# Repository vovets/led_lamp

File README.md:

# led_lamp

Slightly overengineered battery powered LED lamp for reading

## Introduction

The project was born when I acquired a battery powered lamp for reading and very soon found its deficiencies.

* It changed brightness as battery drained.
* It had only 2 brightness level, both too bright.
* Its efficiency which I define as a ratio of power coming to LED to power coming from battery is only 0.7.

So I decided to implement my own led driver with mcu control. It actually required some iterations of software and hardware to come up with what is being described here.

## Requirements

* The brightness should be constant as long as the battery voltage under load is higher than some sensible threshold, say 3V. As battery is drained further brightness may gradually decrease.
* When the battery voltage decreases lower than some defined threshold lamp should provide visual indication that battery needs replacement or charging.
* There should be UI for setting the desired brightness level. The brightness levels may be discreet but then there should be enough different levels. The selected brightness level must be kept across the lamp ON-OFF cycles.
* When the battery is completely drained the lamp should clearly indicate this fact and then turn off to prevent battery damage. Lamp should not turn on with a drained battery but provide indication of the flat battery if possible.
 
## Hardware

The lamp consists of "base" with usb connector and batteries, and "head" with a LED panel and a tactile button. The head connected with the base using flexible metallic tube.

### Original hardware

Original electronics consists of two pcbs, one in head and one in base.
The one in the base contains a usb connector, a diode which blocks current from battery to usb VBUS and a 2 Ohm series resistor.
The head pcb contains unmarked chip which obviously provides PWM capability and on/off/mode logic. The LED panel is controlled by a n-channel mosfet. The gate of the mosfet is controlled by the chip. There is also 2 Ohm resistor in series with LED. I assume that the chip is a some obscure uC and there is no LED current limiting except for series resistors.

### Custom hardware

My custom hardware consists of one pcb which contains all the active elements. I also used original pcbs for passive connections. The original base board is used with all parts removed except USB connector. The original head pcb is also cleared of original parts except the button switch and modified using knife and modwire to provide necessary connections. 3 thin wires run inside the connecting tube.

*My custom pcb front and back respectively*

### Custom hardware schematics discussion

The parts I used to design the schematics are those I had at my disposal and/or could easyly source locally.

#### DC-DC converter

This is the module that provides LED current regulation. Efficiency of the whole device depends mostly on this module.
[Converter chip](hw/datasheet/NCP1529.pdf) may be disabled by MCU via EN pin. In disabled state it consumes just 0.3 uA. Output voltage is controlled by voltage on the FB pin. It is connected to the LED current amplifier.

#### LED current amplifier

The LED current amlifier is built using [MCP6001R](hw/datasheet/MCP6001_1R_1U_2_4.pdf "MCP6001R") CMOS opamp. It amplifies voltage drop on 0.1 Ohm current sensing resistor *R7*, which is fed to the non-inverting input. The non-inverting input is also biased by the DAC module output voltage via *R2*. This arrangement allows to set current regulation point by programming DAC output. When DAC output is 0V, amplifier outputs 0.6V for 250mA LED current. When the voltage on DAC output is at max, which is slightly below 2.5V, the current regulated at approximately 10mA point. It corresponds to the lowest brightness of the lamp.
So the maximum current is 250mA and the minimum is 10mA.

#### DAC

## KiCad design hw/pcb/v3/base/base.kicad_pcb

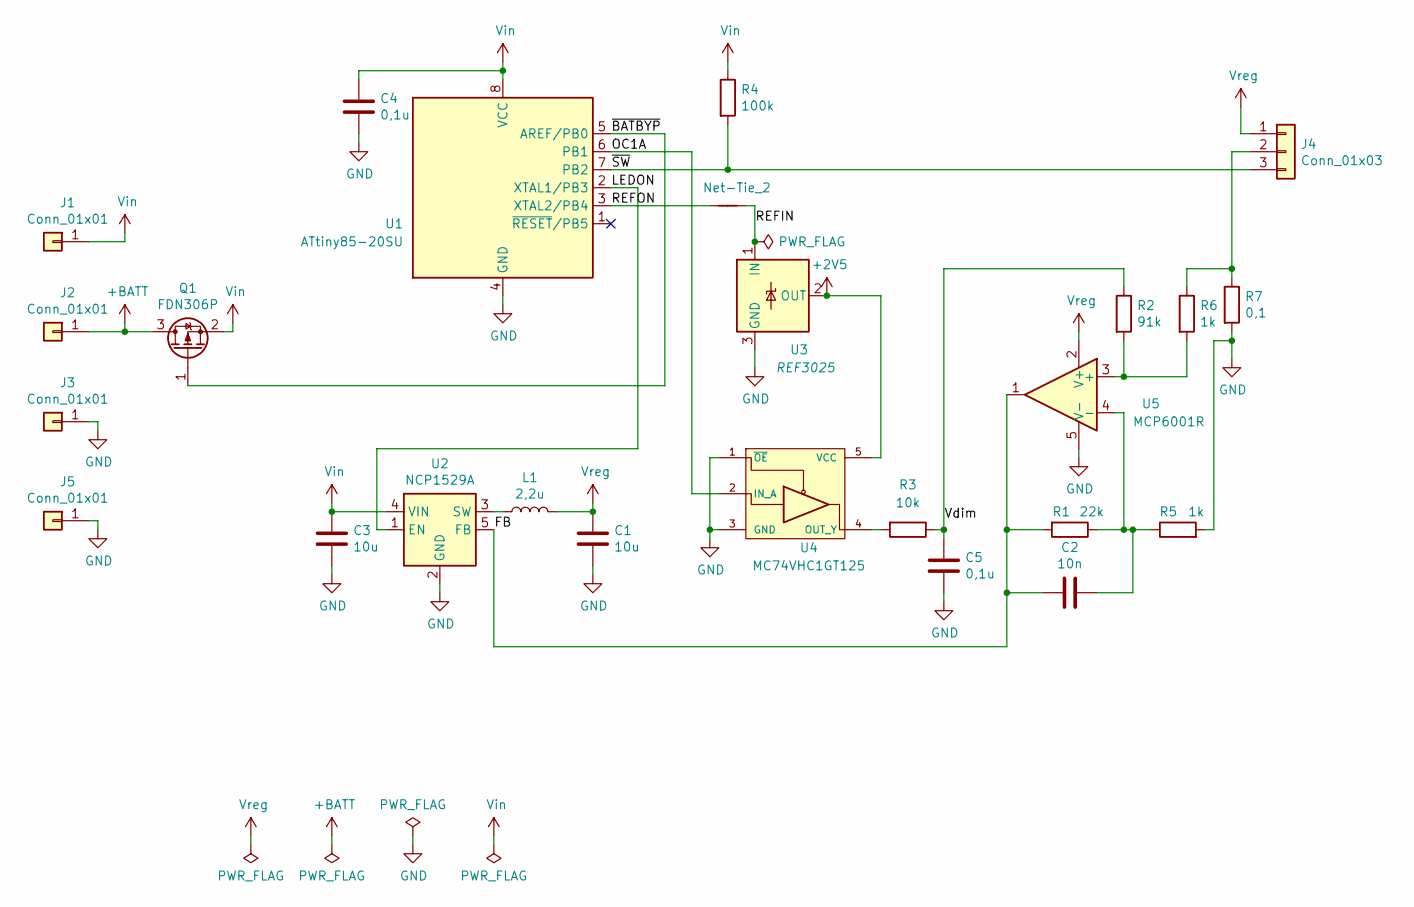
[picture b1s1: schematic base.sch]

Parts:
C1, C3: 10u; C_0805_2012Metric
C2: 10n; C_0805_2012Metric
C4, C5: 0,1u; C_0805_2012Metric
J1, J2, J3, J5: Conn_01x01; SolderWirePad_1x01_SMD_1x2mm
J4: Conn_01x03; SolderWirePad_1x03_SMD_1x2mm
L1: 2,2u; L_1812_4532Metric
NT1: Net-Tie_2; NetTie-2_SMD_Pad0.5mm
Q1: FDN306P; SOT-23
R1: 22k; R_0805_2012Metric
R2: 91k; R_0805_2012Metric
R3: 10k; R_0805_2012Metric
R4: 100k; R_0805_2012Metric
R5, R6: 1k; R_0805_2012Metric
R7: 0,1; R_0805_2012Metric
U1: ATtiny85-20SU; SOIJ-8_5.3x5.3mm_P1.27mm
U2: NCP1529A; SOT-23-5
U3: REF3025; SOT-23
U4: MC74VHC1GT125; SOT-23-5
U5: MCP6001R; SOT-23-5

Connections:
+2V5: U3.2 (OUT), U4.5 (VCC)
+BATT: J2.1, Q1.3 (D)
/FB: C2.2, R1.2, U2.5 (FB), U5.1
/LEDON: U1.2 (XTAL1/PB3), U2.1 (EN)
/OC1A: U1.6 (PB1), U4.2 (IN_A)
/REFIN: NT1.2, U3.1 (IN)
/REFON: NT1.1, U1.3 (XTAL2/PB4)
/Vdim: C5.1, R2.1, R3.1
/~BATBYP: Q1.1 (G), U1.5 (AREF/PB0)
/~SW: J4.3, R4.2, U1.7 (PB2)
GND: C1.2, C3.2, C4.2, C5.2, J3.1, J5.1, R5.2, R7.2, U1.4 (GND), U2.2 (GND), U3.3 (GND), U4.1 (~OE), U4.3 (GND), U5.5 (V-)
unnamed: C2.1, R1.1, R5.1, U5.4 (-)
unnamed: J4.2, R6.1, R7.1
unnamed: L1.1, U2.3 (SW)
unnamed: R2.2, R6.2, U5.3 (+)
unnamed: R3.2, U4.4 (OUT_Y)
Vin: C3.1, C4.1, J1.1, Q1.2 (S), R4.1, U1.8 (VCC), U2.4 (VIN)
Vreg: C1.1, J4.1, L1.2, U5.2 (V+)

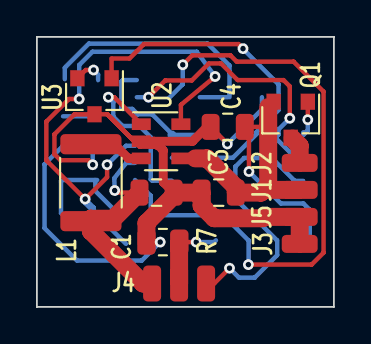
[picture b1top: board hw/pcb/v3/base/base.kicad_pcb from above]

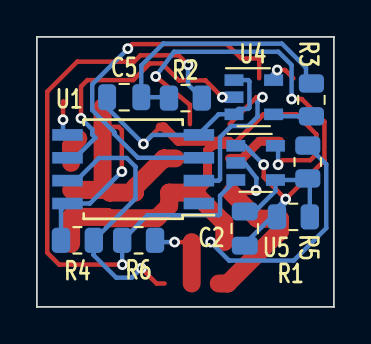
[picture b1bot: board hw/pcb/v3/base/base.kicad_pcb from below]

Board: 2 copper layers, 16.5 x 15.0 mm, 25 parts (11 on the bottom side), 18 nets.

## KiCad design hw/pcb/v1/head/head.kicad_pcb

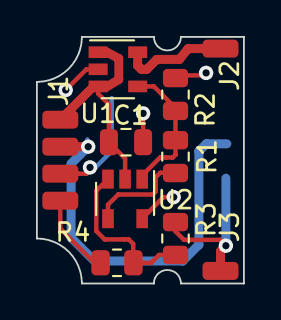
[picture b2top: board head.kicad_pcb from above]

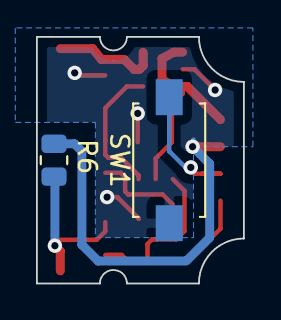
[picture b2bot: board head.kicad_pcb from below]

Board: 2 copper layers, 11.5 x 13.7 mm, 12 parts (2 on the bottom side), 9 nets.

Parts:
C1: 100n; C_0805_2012Metric
J1: Conn_01x04; SolderWirePad_1x04_SMD_1x2mm
J2, J3: Conn_01x01; SolderWirePad_1x01_SMD_1x2mm
R1: 39k; R_0805_2012Metric
R2, R3: 1k; R_0805_2012Metric
R4: 150k; R_0805_2012Metric
R6: 0,1; R_0805_2012Metric
SW1: SW_Push; SW_SPST_UNKNOWN
U1: TPS73601DBV; SOT-23-5
U2: MCP6001R; SOT-23-5

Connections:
/FB: R1.2, R2.1, U1.4, U2.1
/OUT: J2.1, U1.5
/SW: J1.3, SW1.2
/Vpwm: J1.4, R4.1
GND: C1.2, J1.2, R2.2, R6.2, SW1.1, U1.2, U2.5
unnamed: J3.1, R3.1, R6.1
unnamed: R1.1, U2.4
unnamed: R3.2, R4.2, U2.3
Vreg: C1.1, J1.1, U1.1, U1.3, U2.2

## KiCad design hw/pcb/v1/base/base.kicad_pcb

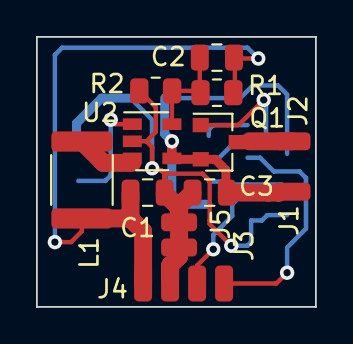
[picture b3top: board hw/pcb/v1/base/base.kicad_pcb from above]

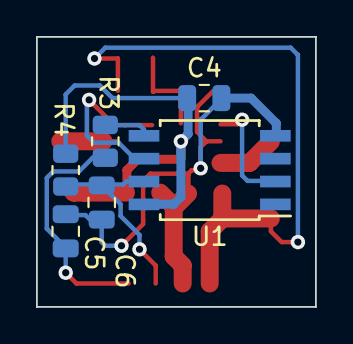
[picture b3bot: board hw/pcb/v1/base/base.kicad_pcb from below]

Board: 2 copper layers, 15.5 x 15.0 mm, 19 parts (6 on the bottom side), 11 nets.

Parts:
C1: 10u; C_0805_2012Metric
C2: 18p; C_0805_2012Metric
C3: 4,7u; C_0805_2012Metric
C4: 0,1u; C_0805_2012Metric
C5, C6: 0.1u; C_0805_2012Metric
J1, J2, J3, J5: Conn_01x01; SolderWirePad_1x01_SMD_1x2mm
J4: Conn_01x04; SolderWirePad_1x04_SMD_1x2mm
L1: 2,2u; L_1812_4532Metric
Q1: FDN306P; SOT-23
R1: 910k; R_0805_2012Metric
R2: 240k; R_0805_2012Metric
R3: 10k; R_0805_2012Metric
R4: 100k; R_0805_2012Metric
U1: ATtiny85-20SU; SOIJ-8_5.3x5.3mm_P1.27mm
U2: NCP1529A; SOT-23-5

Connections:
+BATT: J2.1, Q1.3
/BATBYP: Q1.1, U1.6
/FB: C2.2, R1.2, R2.1, U2.5
/OC0A: R3.2, U1.5
/REGEN: U1.2, U2.1
/SW: C6.1, J4.3, R4.2, U1.7
/Vpwm: C5.1, J4.4, R3.1
GND: C1.2, C3.2, C4.2, C5.2, C6.2, J3.1, J4.2, J5.1, R2.2, U1.4, U2.2
unnamed: L1.1, U2.3
Vin: C3.1, C4.1, J1.1, Q1.2, R4.1, U1.8, U2.4
Vreg: C1.1, C2.1, J4.1, L1.2, R1.1

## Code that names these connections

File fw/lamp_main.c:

#include <lib/timers.h>
#include <lib/blinker.h>
#include "lib/clocks_etc.h"
#include <lib/button.h>
#include <lib/debouncer.h>
#include <lib/pwm.h>
#include <lib/vcc_monitor.h>
#include "debug.h"
#include <lib/stack_check.h>
#include "loop.h"
#include <lib/pwm_animator.h>

#include <stdint.h>
#include <assert.h>

#include <avr/interrupt.h>


#define BATTERY_BYPASS_PIN PB0
#define OC1A_PIN           PB1
#define SWITCH_PIN         PB2
#define LED_ON_PIN         PB3
#define REF_ON_PIN         PB4
#define LED_ON_IS_HIGH true
#define LOW_VOLTAGE_BLINK_PERIOD_S 60

typedef BtnFunc StateFunc;

static void stateOff(BtnEvent e);
static void stateOn(BtnEvent e);
static void stateSetup(BtnEvent e);
static void vccMonitor(uint16_t mV);
static void turnOff_1(void);

typedef struct State {
    enum StateTag {
        StateOff = 0,
        StateOn,
        StateSetup
    } state;
    uint8_t dimLevel;
    uint16_t prevVoltage; // in mV
    uint16_t lowVoltageBlinkCounter;
} State;

static StateFunc state2func[] = {
    stateOff,
    stateOn,
    stateSetup
};


static uint8_t level2dimPercent[] = {
        100, 75, 50, 25, 0
};

static const uint8_t level2dimPercentSize = sizeof(level2dimPercent) / sizeof(level2dimPercent[0]);

static State state;
static Blinker onOffBlinker;
static Blinker vccmBlinker;

static void setState(enum StateTag s) {
    debugTrace2(debugState, s);
    state.state = s;
}

void setupDebug(void) {
    debugTraceEnableIds(
            (uint32_t)0
//            | bits(debugEvPut)
//            | bits(debugEvGet)
//            | bits(debugBtnToggle)
//            | bits(debugBtnEvent)
//            | bits(debugDbnCounter)
//            | bits(debugTimerExpired)
//            | bits(debugTimerSet)
//            | bits(debugTimerCancel)
//            | bits(debugAlarmEnabled)
//            | bits(debugAlarmDisabled)
//            | bits(debugEnterSleep)
//            | bits(debugExitSleep)
//            | bits(debugVccm)
//            | bits(debugState)
//            | bits(debugAdcStartConversion)
            | bits(debugPwm)
    );
}

void initState(void) {
    state.prevVoltage = 0;
}

static void setupPins(void) {
    DDRB |= _BV(OC1A_PIN);
    DDRB |= _BV(BATTERY_BYPASS_PIN);
    DDRB |= _BV(LED_ON_PIN);
    DDRB |= _BV(REF_ON_PIN);
    // disable digital input on all 5 pins except...
    DIDR0 = 0x1FU & ~_BV(SWITCH_PIN);
}

static void setupPCINT(void) {
    PCMSK |= _BV(SWITCH_PIN);
}

static void led(bool on) {
    if (on == LED_ON_IS_HIGH) {
        PORTB |= _BV(LED_ON_PIN);
    } else {
        PORTB &= ~_BV(LED_ON_PIN);
    }
}

static void ref(bool on) {
    if (on) {
        PORTB |= _BV(REF_ON_PIN);
    } else {
        PORTB &= ~_BV(REF_ON_PIN);
    }
}

static void bypass(bool on) {
    if (on) {
        PORTB &= ~_BV(BATTERY_BYPASS_PIN);
    } else {
        PORTB |= _BV(BATTERY_BYPASS_PIN);
    }
}

static uint8_t calculatePwm(uint8_t pwmLevel) {
    uint16_t dimPercent = level2dimPercent[pwmLevel];
    return (dimPercent * 255U) / 100U;
}

static void updatePwm(void) {
    pwmaStart(calculatePwm(state.dimLevel), NULL);
}

static void updateBypass(uint16_t mV) {
    const uint8_t hist = 5;
    int16_t delta = mV - state.prevVoltage;
    if (abs(delta) <= hist) {
        return;
    }
    state.prevVoltage = mV;
    bypass(mV < 4500U);
}

static void vccmBlinkerSetup(uint8_t iterations) {
    blinkerSetup(&vccmBlinker, BlinkerModeOffThenOn, iterations, ST_MS2TICKS(50), ST_MS2TICKS(100), &led);
}

static void vccmBlinkerFinished(Blinker* blinker, void* off) {
    if (off) {
        turnOff_1();
    }
}

static void checkLowVoltage(uint16_t mV) {
    if (mV < 2700) {
        vccmBlinkerSetup(5);
        blinkerStart(&vccmBlinker, &vccmBlinkerFinished, (void*)1);
    } else if (mV >= 2700 && mV < 3100) {
        if (state.lowVoltageBlinkCounter) {
            --state.lowVoltageBlinkCounter;
        } else {
            state.lowVoltageBlinkCounter = (LOW_VOLTAGE_BLINK_PERIOD_S * 1000UL) / VCC_MONITOR_PERIOD_MS;
            vccmBlinkerSetup(3);
            blinkerStart(&vccmBlinker, &vccmBlinkerFinished, (void*)0);
        }
    }
}

static void vccMonitor(uint16_t mV) {
    debugTrace2(debugVccm, mV);
    updateBypass(mV);
    checkLowVoltage(mV);
    vccmContinue(&vccMonitor);
}

static void setupBlinker(void) {
    blinkerSetup(&onOffBlinker, BlinkerModeOffThenOn, 1, ST_MS2TICKS(100), ST_MS2TICKS(400), &led);
}

static void startBlinker(void) {
    if (!blinkerIsActive(&onOffBlinker)) {
        blinkerStart(&onOffBlinker, 0, 0);
    }
}

static void stopBlinker(void) {
    if (blinkerIsActive(&onOffBlinker)) {
        blinkerStop(&onOffBlinker);
    }
}

static void turnOn(void) {
    setState(StateOn);
    ref(true);
    pwmSet(255U);
    pwmEnable();
    vccmEnable();
    vccmStart(&vccMonitor);
    led(true);
    updatePwm();
}

static void turnOff_1(void) {
    setState(StateOff);
    vccmDisable();
    state.lowVoltageBlinkCounter = 0;
    stopBlinker();
    led(false);
    ref(false);
    pwmaStop();
    pwmDisable();
}

static void turnOff_0(void) {
    pwmaStart(255, &turnOff_1);
}

static void enterSetup() {
    setState(StateSetup);
    startBlinker();
}

static void exitSetup(void) {
    setState(StateOn);
    startBlinker();
}

static void nextLevel(void) {
    state.dimLevel = (state.dimLevel + 1) % level2dimPercentSize;
    updatePwm();
}

static void stateOff(BtnEvent e) {
    switch (e) {
        case BtnShortPress:
            turnOn();
            break;

        default:
            ;
    }
}

static void stateOn(BtnEvent e) {
    switch (e) {
        case BtnShortPress:
            turnOff_0();
            break;

        case BtnLongPress:
            enterSetup();
            break;

        default:
            ;
    }
}

static void stateSetup(BtnEvent e) {
    switch (e) {
        case BtnLongPress:
            exitSetup();
            break;

        case BtnShortPress:
            nextLevel();
            break;

        default:
            ;
    }
}

uint8_t sleepMode(void) {
    if (state.state == StateOff && !stIsAlarmSet()) {
        return SLEEP_MODE_PWR_DOWN;
    }
    return SLEEP_MODE_IDLE;
}

static void buttonEvent(BtnEvent e) {
    debugTrace2(debugBtnEvent, e);
    state2func[state.state](e);
}

int main(void) __attribute__ ((noreturn));

int main(void)
{
    setupDebug();
    led(false);
    bypass(false);
    initState();
    setupClock();
    setupPins();
    pwmInit();
    stInit();
    tmInit();
    btnInit(SWITCH_PIN, buttonEvent);
    setupPCINT();
    setupBlinker();
    vccmInit();
    dbnEnable();
    stEnableClock();
    sei();
    loop();
}

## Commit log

2021-12-17 fw initial commit
2022-01-03 Added v1 pcb, just for reference.
2022-01-03 Added some datasheets.
2022-01-24 Everything seem to work
2022-01-24 Added submodule for Unity unittest library
2022-01-24 Added docs on TI logic components
2022-01-24 Low voltage blinker period constant is in seconds
2022-02-19 Bugfixes, directory structure changes, refactoring
    * Fixed: use of |= operator with interrupt mask registers. Do not use |= on registers with address > 0x20. SBI instructin work only for addresses < 0x20. Without sbi, compiler generates read-apply_or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
    * Fixed: use of stNow (instead of stNowI) from interrupt context unintentionally enables interrupts
    * Separate directories for apps, use static include names for per app parameter files
    * Put common files for all apps into lib directory
    * Use panic() for unrecoverable errors and asserts instead of abort()
    * Use assert_() macro
2022-02-19 Actual working schematics, pcb needs updating. Prototype uses modwires for now.
    * Added simple dac using voltage reference and cmos buffer
2022-03-23 Inplemented and tested v3 hardware
    * One base board instead of base and head boards
    * Removed linear regulator
    * 88% efficiency of battery to LED conversion
2022-03-24 Added some content to README.md
2022-03-28 Added some info to README.md
